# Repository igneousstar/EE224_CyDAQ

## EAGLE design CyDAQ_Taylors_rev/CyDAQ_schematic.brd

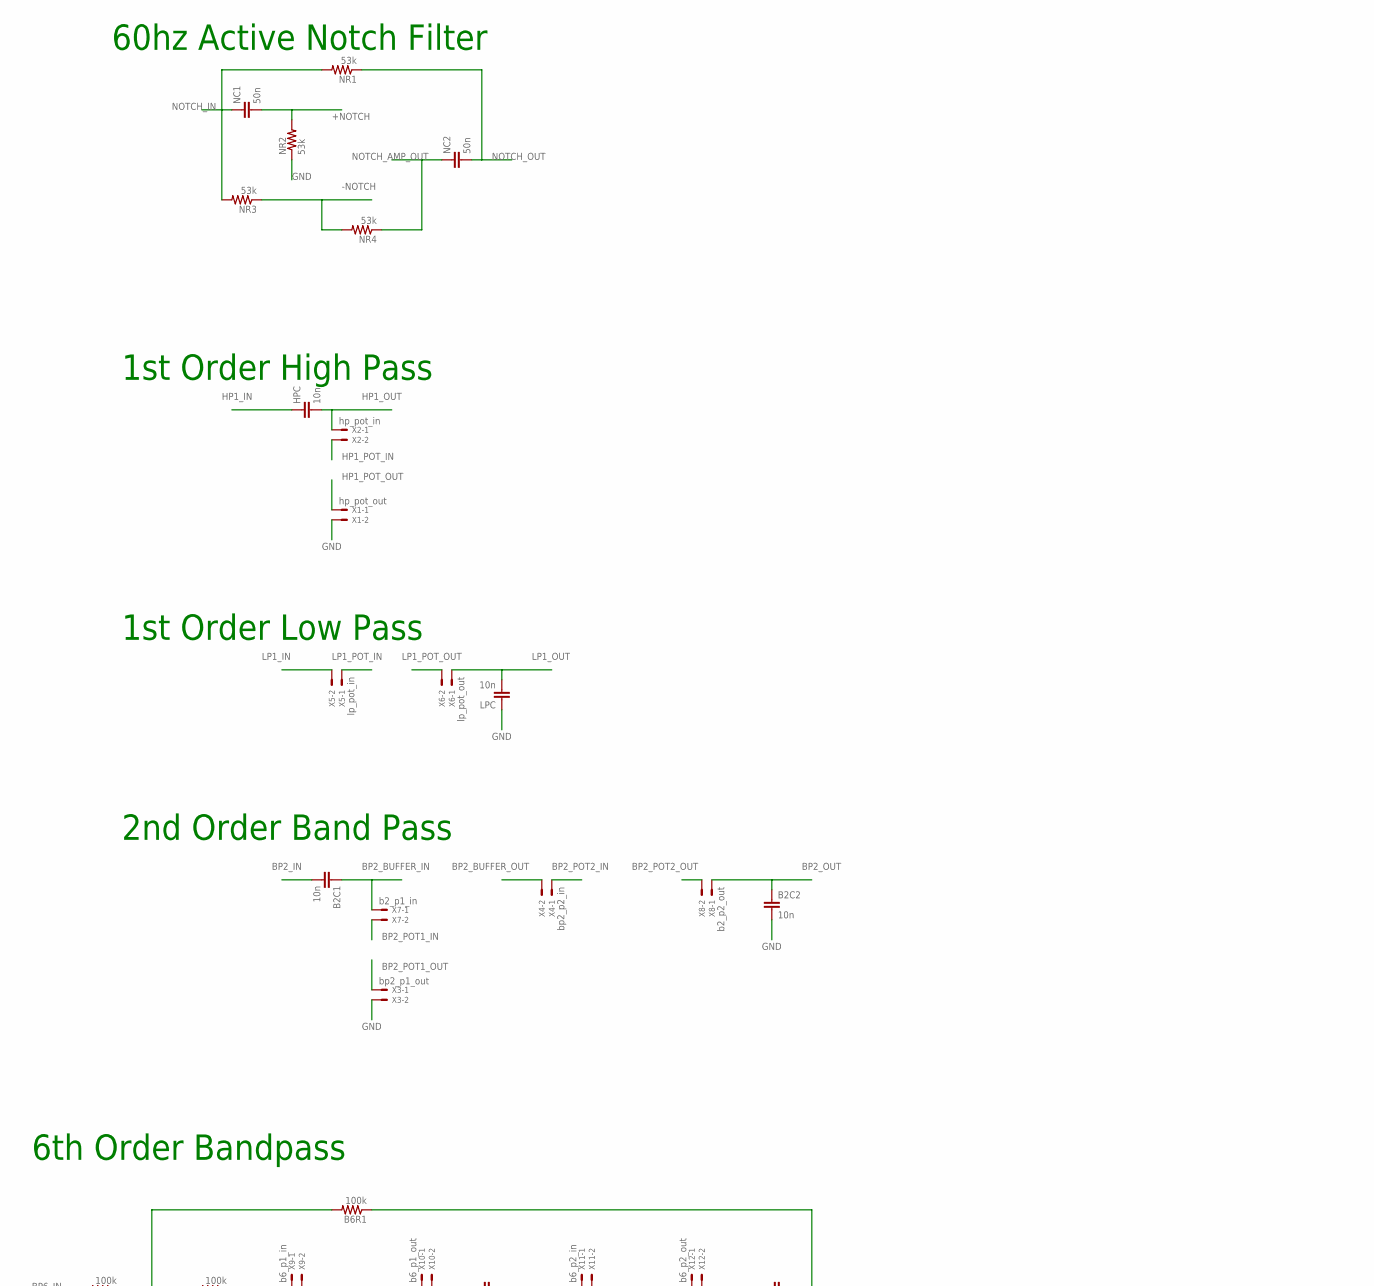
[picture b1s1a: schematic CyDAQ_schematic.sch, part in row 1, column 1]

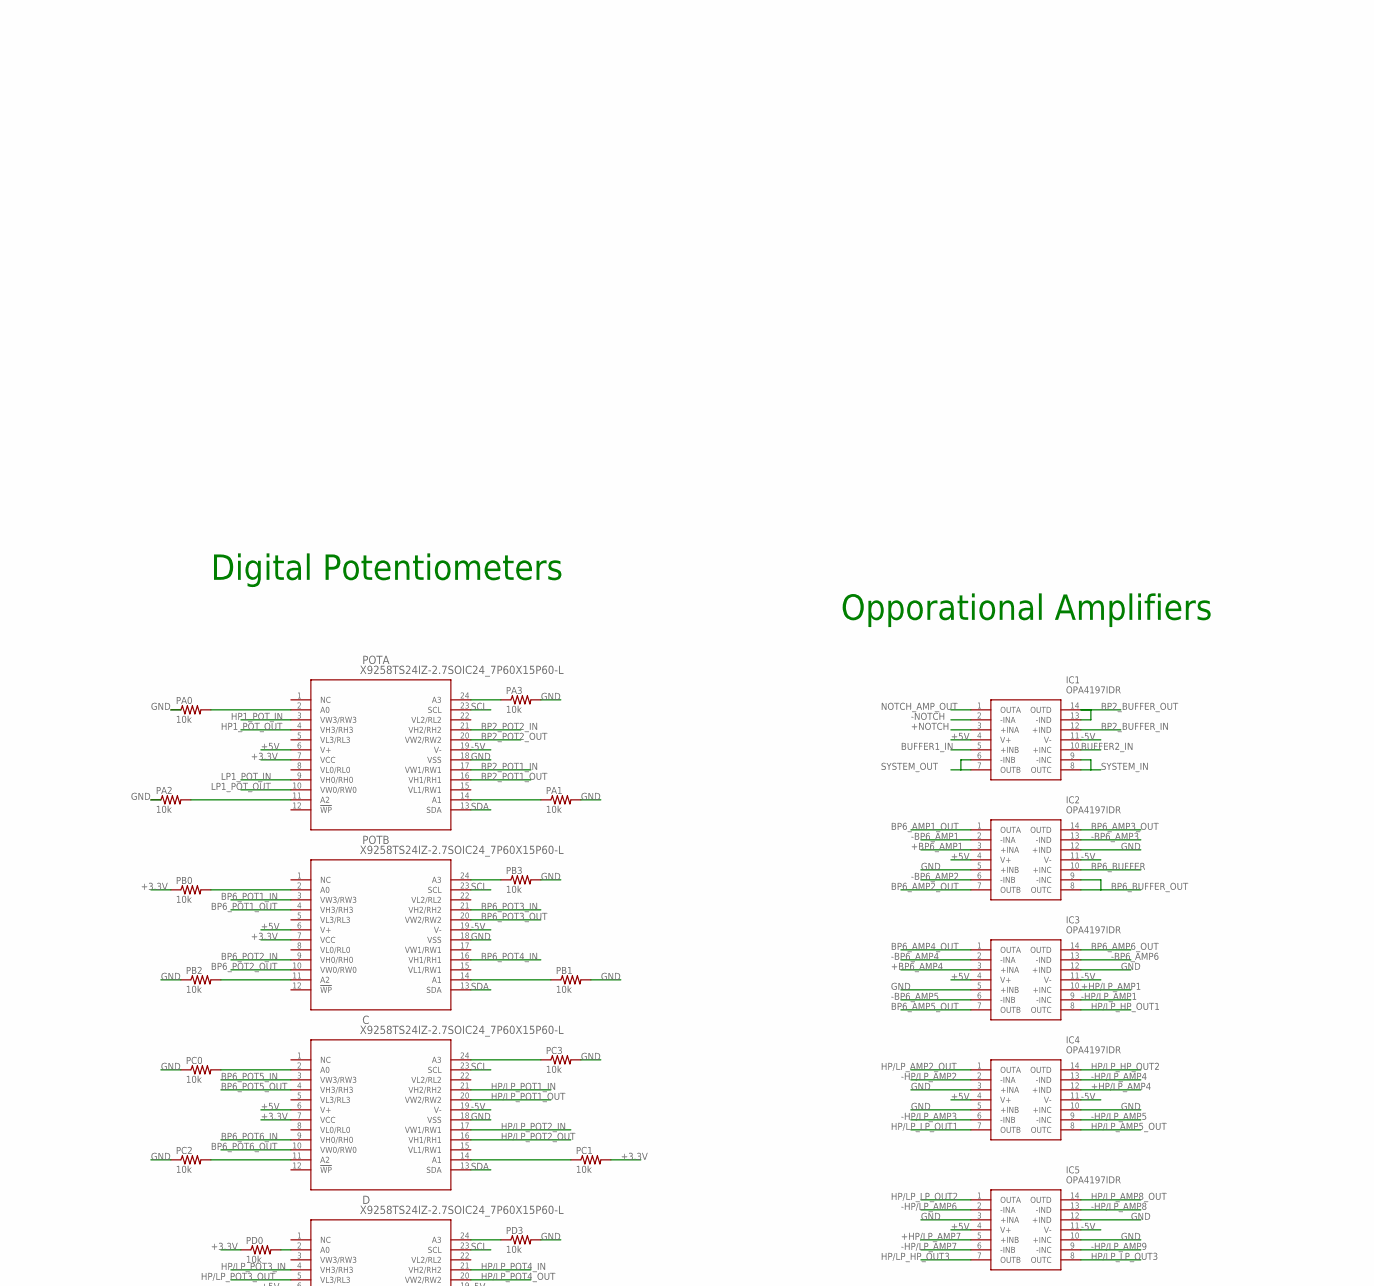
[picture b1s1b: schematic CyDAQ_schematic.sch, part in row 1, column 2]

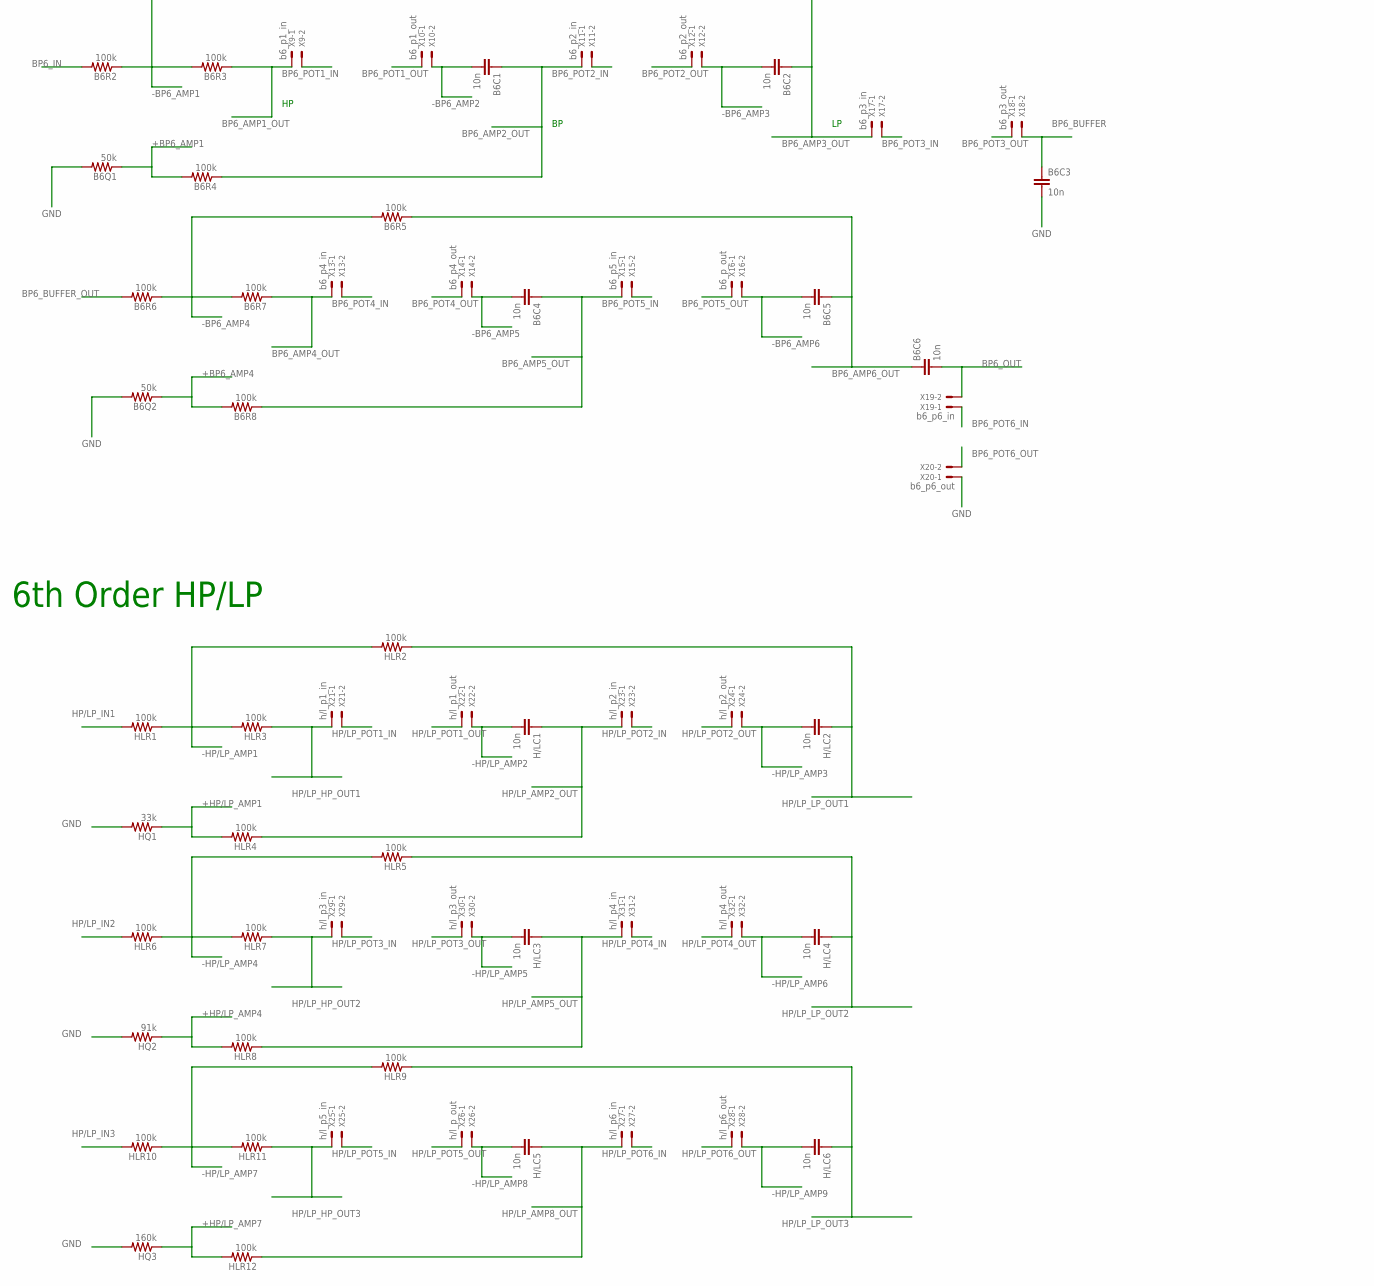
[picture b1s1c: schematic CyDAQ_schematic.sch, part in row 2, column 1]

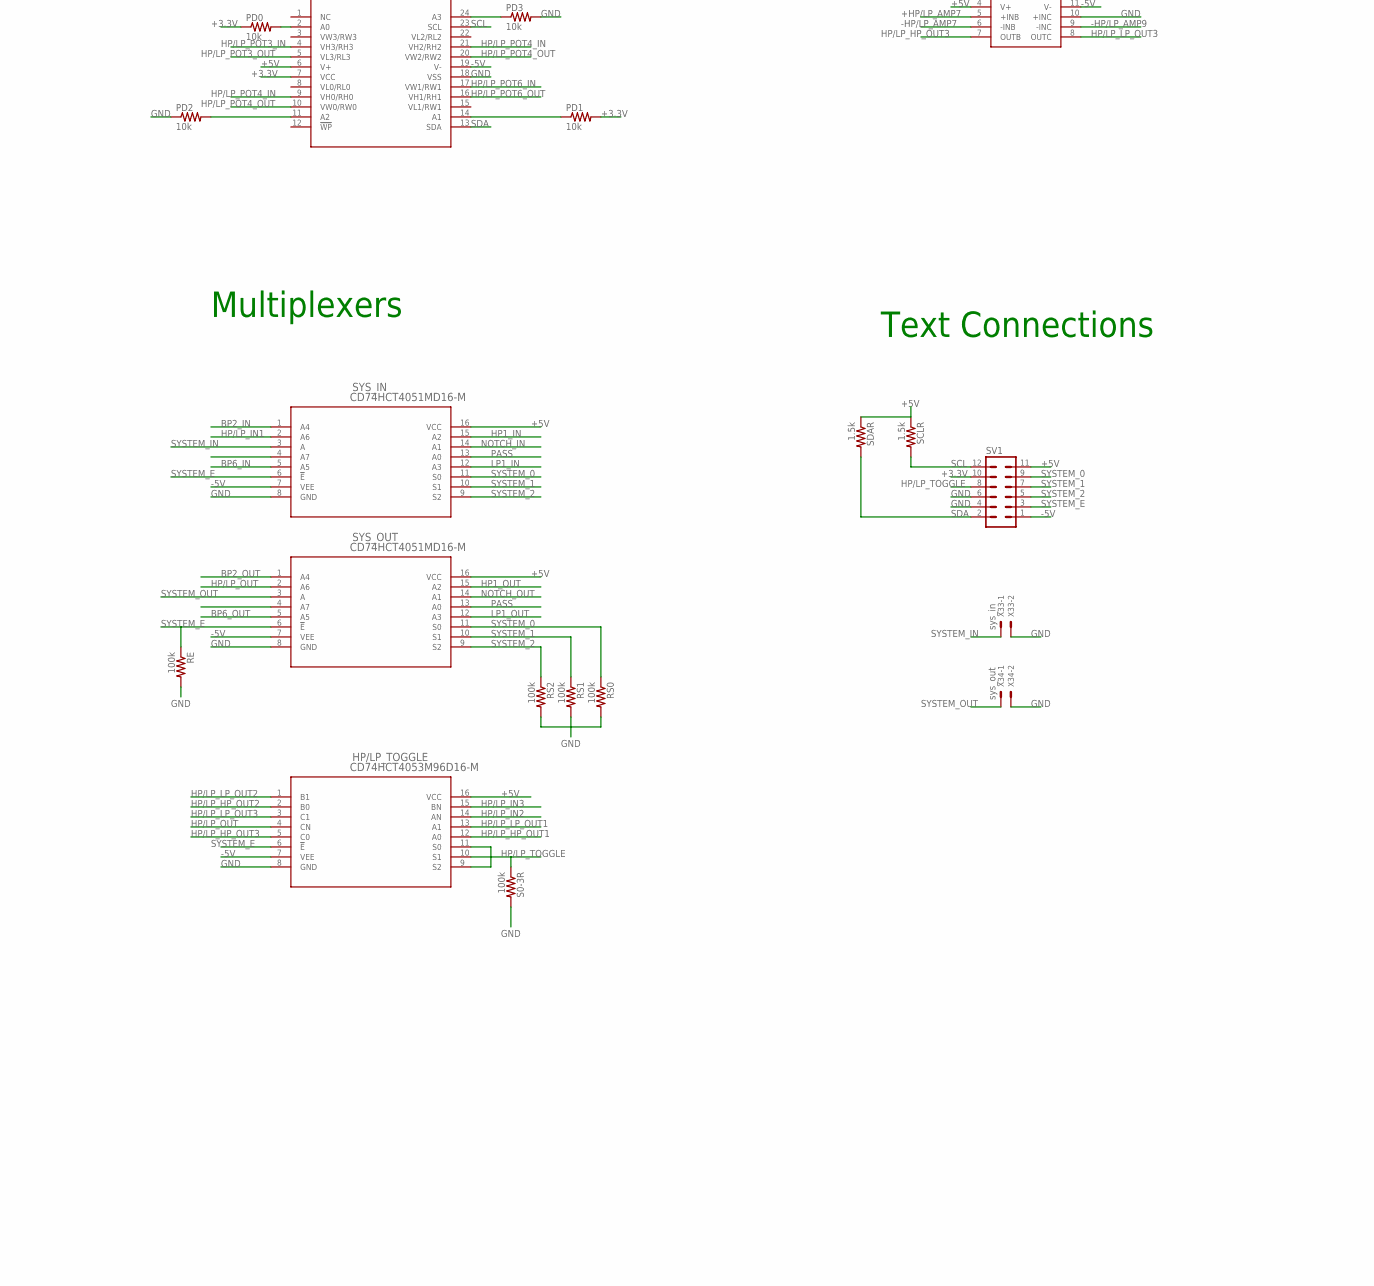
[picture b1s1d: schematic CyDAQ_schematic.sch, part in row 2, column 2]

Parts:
B2C1, B2C2, B6C1, B6C2, B6C3, B6C4, B6C5, B6C6: 10n; C0805K
B6Q1, B6Q2: 50k; R0805W
B6R1, B6R2, B6R3, B6R4, B6R5, B6R6, B6R7, B6R8: 100k; R0805W
C: X9258TS24IZ-2.7SOIC24_7P60X15P60-L; SOIC24_7P60X15P60-L
D: X9258TS24IZ-2.7SOIC24_7P60X15P60-L; SOIC24_7P60X15P60-L
H/LC1, H/LC2, H/LC3, H/LC4, H/LC5, H/LC6: 10n; C0805K
HLR1, HLR2, HLR3, HLR4, HLR5, HLR6, HLR7, HLR8, HLR9, HLR10, HLR11, HLR12: 100k; R0805W
HP/LP_TOGGLE: CD74HCT4053M96D16-M; D16-M
HPC: 10n; C0805K
HQ1: 33k; R0805W
HQ2: 91k; R0805W
HQ3: 160k; R0805W
IC1, IC2, IC3, IC4, IC5: OPA4197IDR; SOIC127P600X175-14N
LPC: 10n; C0805K
NC1, NC2: 50n; C0805K
NR1, NR2, NR3, NR4: 53k; R0805W
PA0, PA1, PA2, PA3: 10k; R0805W
PB0, PB1, PB2, PB3: 10k; R0805W
PC0, PC1, PC2, PC3: 10k; R0805W
PD0, PD1, PD2, PD3: 10k; R0805W
POTA: X9258TS24IZ-2.7SOIC24_7P60X15P60-L; SOIC24_7P60X15P60-L
POTB: X9258TS24IZ-2.7SOIC24_7P60X15P60-L; SOIC24_7P60X15P60-L
RE: 100k; R0805W
RS0, RS1, RS2: 100k; R0805W
S0-3R: 100k; R0805W
SCLR: 1.5k; R0805W
SDAR: 1.5k; R0805W
SV1: MA06-2
SYS_IN: CD74HCT4051MD16-M; D16-M
SYS_OUT: CD74HCT4051MD16-M; D16-M
X1: hp_pot_out; 22-23-2021
X2: hp_pot_in; 22-23-2021
X3: bp2_p1_out; 22-23-2021
X4: bp2_p2_in; 22-23-2021
X5: lp_pot_in; 22-23-2021
X6: lp_pot_out; 22-23-2021
X7: b2_p1_in; 22-23-2021
X8: b2_p2_out; 22-23-2021
X9: b6_p1_in; 22-23-2021
X10: b6_p1_out; 22-23-2021
X11: b6_p2_in; 22-23-2021
X12: b6_p2_out; 22-23-2021
X13: b6_p4_in; 22-23-2021
X14: b6_p4_out; 22-23-2021
X15: b6_p5_in; 22-23-2021
X16: b6_p_out; 22-23-2021
X17: b6_p3_in; 22-23-2021
X18: b6_p3_out; 22-23-2021
X19: b6_p6_in; 22-23-2021
X20: b6_p6_out; 22-23-2021
X21: h/l_p1_in; 22-23-2021
X22: h/l_p1_out; 22-23-2021
X23: h/l_p2_in; 22-23-2021
X24: h/l_p2_out; 22-23-2021
X25: h/l_p5_in; 22-23-2021
X26: h/l_p_out; 22-23-2021
X27: h/l_p6_in; 22-23-2021
X28: h/l_p6_out; 22-23-2021
X29: h/l_p3_in; 22-23-2021
X30: h/l_p3_out; 22-23-2021
X31: h/l_p4_in; 22-23-2021
X32: h/l_p4_out; 22-23-2021
X33: sys_in; 22-23-2021
X34: sys_out; 22-23-2021

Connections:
+3.3V: C.7 (VCC), D.7 (VCC), PB0.1, PC1.2, PD0.1, PD1.2, POTA.7 (VCC), POTB.7 (VCC), SV1.10
+5V: C.6 (V+), D.6 (V+), HP/LP_TOGGLE.16 (VCC), IC1.4 (V+), IC2.4 (V+), IC3.4 (V+), IC4.4 (V+), IC5.4 (V+), POTA.6 (V+), POTB.6 (V+), SCLR.1, SDAR.1, SV1.11, SYS_IN.16 (VCC), SYS_OUT.16 (VCC)
+BP6_AMP1: B6Q1.1, B6R4.2, IC2.3 (+INA)
+BP6_AMP4: B6Q2.1, B6R8.2, IC3.3 (+INA)
+HP/LP_AMP1: HLR4.2, HQ1.1, IC3.10 (+INC)
+HP/LP_AMP4: HLR8.2, HQ2.1, IC4.12 (+IND)
+HP/LP_AMP7: HLR12.2, HQ3.1, IC5.5 (+INB)
+NOTCH: IC1.3 (+INA), NC1.2, NR2.2
-5V: C.19 (V-), D.19 (V-), HP/LP_TOGGLE.7 (VEE), IC1.11 (V-), IC2.11 (V-), IC3.11 (V-), IC4.11 (V-), IC5.11 (V-), POTA.19 (V-), POTB.19 (V-), SV1.1, SYS_IN.7 (VEE), SYS_OUT.7 (VEE)
-BP6_AMP1: B6R1.2, B6R2.1, B6R3.2, IC2.2 (-INA)
-BP6_AMP2: B6C1.2, IC2.6 (-INB), X10.2
-BP6_AMP3: B6C2.2, IC2.13 (-IND), X12.2
-BP6_AMP4: B6R5.2, B6R6.1, B6R7.2, IC3.2 (-INA)
-BP6_AMP5: B6C4.2, IC3.6 (-INB), X14.2
-BP6_AMP6: B6C5.2, IC3.13 (-IND), X16.2
-HP/LP_AMP1: HLR1.1, HLR2.2, HLR3.2, IC3.9 (-INC)
-HP/LP_AMP2: H/LC1.2, IC4.2 (-INA), X22.2
-HP/LP_AMP3: H/LC2.2, IC4.6 (-INB), X24.2
-HP/LP_AMP4: HLR5.2, HLR6.1, HLR7.2, IC4.13 (-IND)
-HP/LP_AMP5: H/LC3.2, IC4.9 (-INC), X30.2
-HP/LP_AMP6: H/LC4.2, IC5.2 (-INA), X32.2
-HP/LP_AMP7: HLR9.2, HLR10.1, HLR11.2, IC5.6 (-INB)
-HP/LP_AMP8: H/LC5.2, IC5.13 (-IND), X26.2
-HP/LP_AMP9: H/LC6.2, IC5.9 (-INC), X28.2
-NOTCH: IC1.2 (-INA), NR3.1, NR4.2
BP2_BUFFER_IN: B2C1.1, IC1.12 (+IND), X7.1
BP2_BUFFER_OUT: IC1.13 (-IND), IC1.14 (OUTD), X4.2
BP2_IN: B2C1.2, SYS_IN.1 (A4)
BP2_OUT: B2C2.1, SYS_OUT.1 (A4), X8.1
BP2_POT1_IN: POTA.17 (VW1/RW1), X7.2
BP2_POT1_OUT: POTA.16 (VH1/RH1), X3.1
BP2_POT2_IN: POTA.21 (VH2/RH2), X4.1
BP2_POT2_OUT: POTA.20 (VW2/RW2), X8.2
BP6_AMP1_OUT: B6R3.1, IC2.1 (OUTA), X9.1
BP6_AMP2_OUT: B6C1.1, B6R4.1, IC2.7 (OUTB), X11.1
BP6_AMP3_OUT: B6C2.1, B6R1.1, IC2.14 (OUTD), X17.1
BP6_AMP4_OUT: B6R7.1, IC3.1 (OUTA), X13.1
BP6_AMP5_OUT: B6C4.1, B6R8.1, IC3.7 (OUTB), X15.1
BP6_AMP6_OUT: B6C5.1, B6C6.1, B6R5.1, IC3.14 (OUTD)
BP6_BUFFER: B6C3.1, IC2.10 (+INC), X18.2
BP6_BUFFER_OUT: B6R6.2, IC2.8 (OUTC), IC2.9 (-INC)
BP6_IN: B6R2.2, SYS_IN.5 (A5)
BP6_OUT: B6C6.2, SYS_OUT.5 (A5), X19.2
BP6_POT1_IN: POTB.3 (VW3/RW3), X9.2
BP6_POT1_OUT: POTB.4 (VH3/RH3), X10.1
BP6_POT2_IN: POTB.9 (VH0/RH0), X11.2
BP6_POT2_OUT: POTB.10 (VW0/RW0), X12.1
BP6_POT3_IN: POTB.21 (VH2/RH2), X17.2
BP6_POT3_OUT: POTB.20 (VW2/RW2), X18.1
BP6_POT4_IN: POTB.16 (VH1/RH1), X13.2
BP6_POT4_OUT: X14.1
BP6_POT5_IN: C.3 (VW3/RW3), X15.2
BP6_POT5_OUT: C.4 (VH3/RH3), X16.1
BP6_POT6_IN: C.9 (VH0/RH0), X19.1
BP6_POT6_OUT: C.10 (VW0/RW0), X20.2
BUFFER1_IN: IC1.5 (+INB)
BUFFER2_IN: IC1.10 (+INC)
GND: B2C2.2, B6C3.2, B6Q1.2, B6Q2.2, C.18 (VSS), D.18 (VSS), HP/LP_TOGGLE.8 (GND), HQ1.2, HQ2.2, HQ3.2, IC2.5 (+INB), IC2.12 (+IND), IC3.5 (+INB), IC3.12 (+IND), IC4.3 (+INA), IC4.5 (+INB), IC4.10 (+INC), IC5.3 (+INA), IC5.10 (+INC), IC5.12 (+IND), LPC.1, NR2.1, PA0.1, PA1.2, PA2.1, PA3.2, PB1.2, PB2.1, PB3.2, PC0.1, PC2.1, PC3.2, PD2.1, PD3.2, POTA.18 (VSS), POTB.18 (VSS), RE.2, RS0.2, RS1.2, RS2.2, S0-3R.2, SV1.4, SV1.6, SYS_IN.8 (GND), SYS_OUT.8 (GND), X1.2, X3.2, X20.1, X33.2, X34.2
HP1_IN: HPC.1, SYS_IN.15 (A2)
HP1_OUT: HPC.2, SYS_OUT.15 (A2), X2.1
HP1_POT_IN: POTA.3 (VW3/RW3), X2.2
HP1_POT_OUT: POTA.4 (VH3/RH3), X1.1
HP/LP_AMP2_OUT: H/LC1.1, HLR4.1, IC4.1 (OUTA), X23.1
HP/LP_AMP5_OUT: H/LC3.1, HLR8.1, IC4.8 (OUTC), X31.1
HP/LP_AMP8_OUT: H/LC5.1, HLR12.1, IC5.14 (OUTD), X27.1
HP/LP_HP_OUT1: HLR3.1, HP/LP_TOGGLE.12 (A0), IC3.8 (OUTC), X21.1
HP/LP_HP_OUT2: HLR7.1, HP/LP_TOGGLE.2 (B0), IC4.14 (OUTD), X29.1
HP/LP_HP_OUT3: HLR11.1, HP/LP_TOGGLE.5 (C0), IC5.7 (OUTB), X25.1
HP/LP_IN1: HLR1.2, SYS_IN.2 (A6)
HP/LP_IN2: HLR6.2, HP/LP_TOGGLE.14 (AN)
HP/LP_IN3: HLR10.2, HP/LP_TOGGLE.15 (BN)
HP/LP_LP_OUT1: H/LC2.1, HLR2.1, HP/LP_TOGGLE.13 (A1), IC4.7 (OUTB)
HP/LP_LP_OUT2: H/LC4.1, HLR5.1, HP/LP_TOGGLE.1 (B1), IC5.1 (OUTA)
HP/LP_LP_OUT3: H/LC6.1, HLR9.1, HP/LP_TOGGLE.3 (C1), IC5.8 (OUTC)
HP/LP_OUT: HP/LP_TOGGLE.4 (CN), SYS_OUT.2 (A6)
HP/LP_POT1_IN: C.21 (VH2/RH2), X21.2
HP/LP_POT1_OUT: C.20 (VW2/RW2), X22.1
HP/LP_POT2_IN: C.17 (VW1/RW1), X23.2
HP/LP_POT2_OUT: C.16 (VH1/RH1), X24.1
HP/LP_POT3_IN: D.4 (VH3/RH3), X29.2
HP/LP_POT3_OUT: D.5 (VL3/RL3), X30.1
HP/LP_POT4_IN: D.9 (VH0/RH0), D.21 (VH2/RH2), X31.2
HP/LP_POT4_OUT: D.10 (VW0/RW0), D.20 (VW2/RW2), X32.1
HP/LP_POT5_IN: X25.2
HP/LP_POT5_OUT: X26.1
HP/LP_POT6_IN: D.17 (VW1/RW1), X27.2
HP/LP_POT6_OUT: D.16 (VH1/RH1), X28.1
HP/LP_TOGGLE: HP/LP_TOGGLE.9 (S2), HP/LP_TOGGLE.10 (S1), HP/LP_TOGGLE.11 (S0), S0-3R.1, SV1.8
LP1_IN: SYS_IN.12 (A3), X5.2
LP1_OUT: LPC.2, SYS_OUT.12 (A3), X6.1
LP1_POT_IN: POTA.9 (VH0/RH0), X5.1
LP1_POT_OUT: POTA.10 (VW0/RW0), X6.2
unnamed: PA0.2, POTA.2 (A0)
unnamed: PA2.2, POTA.11 (A2)
unnamed: PA1.1, POTA.14 (A1)
unnamed: PA3.1, POTA.24 (A3)
unnamed: PB0.2, POTB.2 (A0)
unnamed: PB2.2, POTB.11 (A2)
unnamed: PB1.1, POTB.14 (A1)
unnamed: PB3.1, POTB.24 (A3)
unnamed: C.2 (A0), PC0.2
unnamed: C.11 (A2), PC2.2
unnamed: C.14 (A1), PC1.1
unnamed: C.24 (A3), PC3.1
unnamed: D.2 (A0), PD0.2
unnamed: D.11 (A2), PD2.2
unnamed: D.14 (A1), PD1.1
unnamed: D.24 (A3), PD3.1
NOTCH_AMP_OUT: IC1.1 (OUTA), NC2.1, NR4.1
NOTCH_IN: NC1.1, NR1.2, NR3.2, SYS_IN.14 (A1)
NOTCH_OUT: NC2.2, NR1.1, SYS_OUT.14 (A1)
PASS: SYS_IN.13 (A0), SYS_OUT.13 (A0)
SCL: C.23 (SCL), D.23 (SCL), POTA.23 (SCL), POTB.23 (SCL), SCLR.2, SV1.12
SDA: C.13 (SDA), D.13 (SDA), POTA.13 (SDA), POTB.13 (SDA), SDAR.2, SV1.2
SYSTEM_0: RS0.1, SV1.9, SYS_IN.11 (S0), SYS_OUT.11 (S0)
SYSTEM_1: RS1.1, SV1.7, SYS_IN.10 (S1), SYS_OUT.10 (S1)
SYSTEM_2: RS2.1, SV1.5, SYS_IN.9 (S2), SYS_OUT.9 (S2)
SYSTEM_E: HP/LP_TOGGLE.6 (!E), RE.1, SV1.3, SYS_IN.6 (!E), SYS_OUT.6 (!E)
SYSTEM_IN: IC1.8 (OUTC), IC1.9 (-INC), SYS_IN.3 (A), X33.1
SYSTEM_OUT: IC1.6 (-INB), IC1.7 (OUTB), SYS_OUT.3 (A), X34.1

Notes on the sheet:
60hz Active Notch Filter
1st Order High Pass
1st Order Low Pass
2nd Order Band Pass
6th Order Bandpass
6th Order HP/LP
Multiplexers
Digital Potentiometers
Opporational Amplifiers
Text Connections

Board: 2 copper layers, 117 parts (0 on the bottom side), 115 nets, no tracks yet.

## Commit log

2019-02-21 Create LICENSE
